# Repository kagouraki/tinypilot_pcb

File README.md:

# tinypilot_pcb
This is my pcb for tinypilot

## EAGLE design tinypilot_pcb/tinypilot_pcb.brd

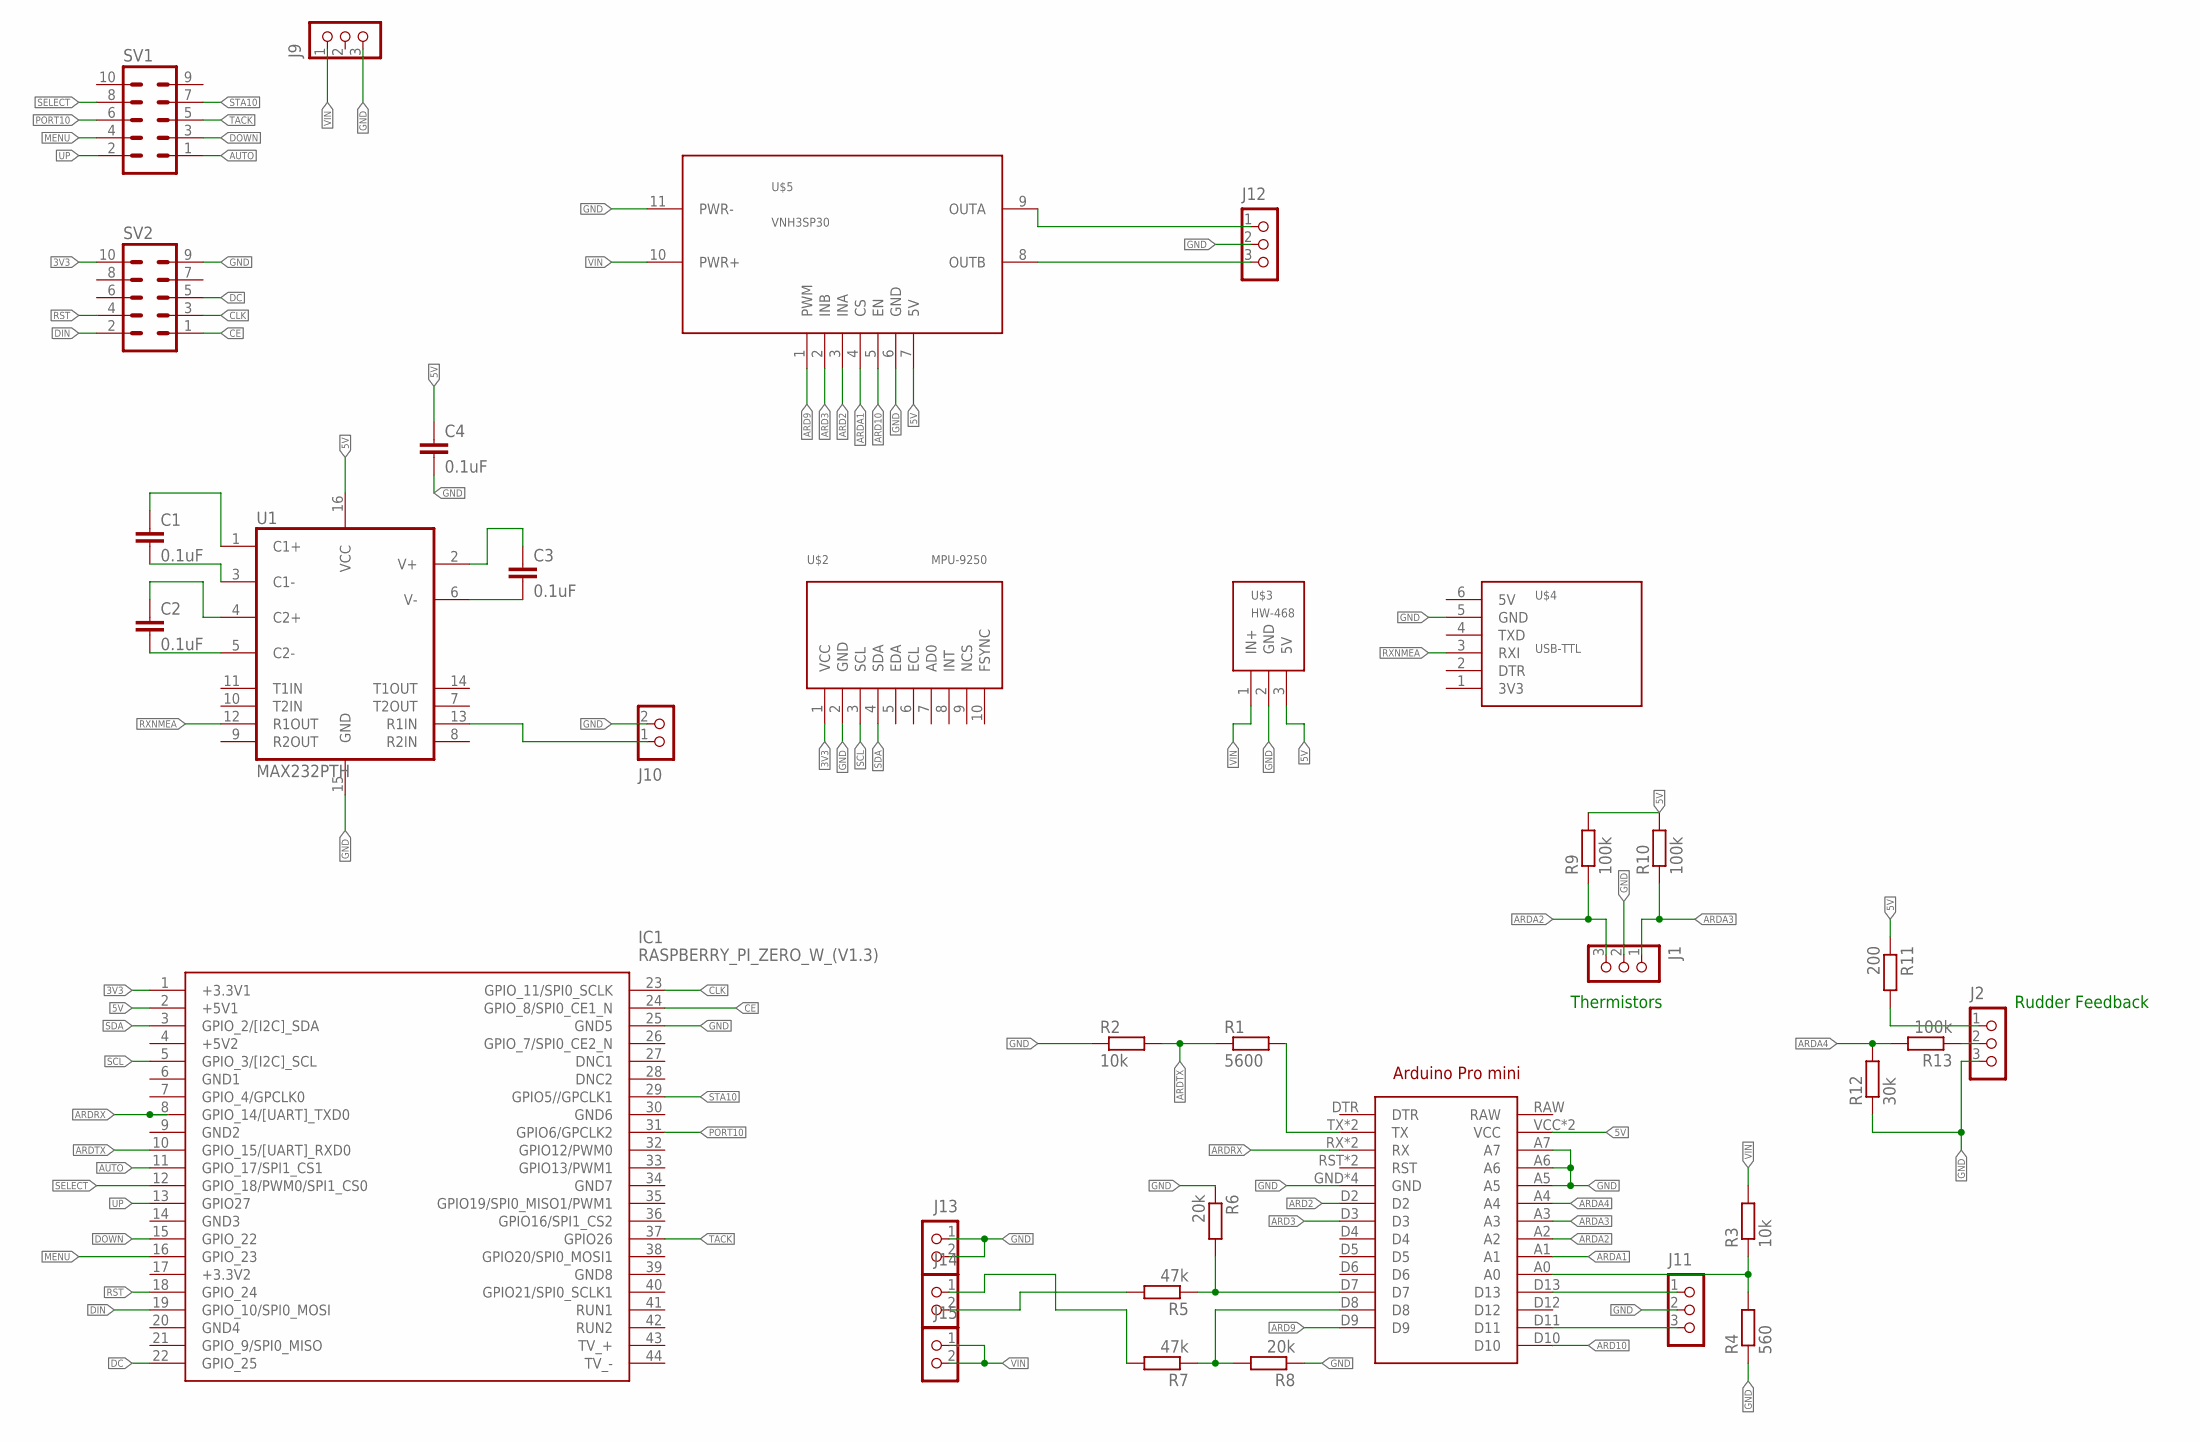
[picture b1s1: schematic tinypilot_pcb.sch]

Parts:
ARDUINO1: ARDUINO_PRO_MINI
C1, C2, C3, C4: 0.1uF; CAP-PTH-5MM
IC1: RASPBERRY_PI_ZERO_W_(V1.3); RASPBERRYPIZEROWV13
J1, J2, J9, J11, J12: CON_TERMINAL_BLOCK_03-5MM; TERMINAL_BLOCK_3P_5
J10, J13, J14, J15: CON_TERMINAL_BLOCK_02-5MM; TERMINAL_BLOCK_2P_5
R1: 5600; 0207/10
R2, R3: 10k; 0207/10
R4: 560; 0207/10
R5, R7: 47k; 0207/10
R6, R8: 20k; 0207/10
R9, R10, R13: 100k; 0207/10
R11: 200; 0207/10
R12: 30k; 0207/10
SV1, SV2: ML10
U1: MAX232PTH; DIL16
U$2: MPU-9250
U$3: HW-468
U$4: USB-TTL
U$5: VNH3SP30

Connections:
3V3: IC1.1 (+3.3V1), SV2.10, U$2.1 (VCC)
5V: ARDUINO1.VCC, ARDUINO1.VCC@1 (VCC), C4.1, IC1.2 (+5V1), R9.2, R10.2, R11.1, U1.16 (VCC), U$3.3 (5V), U$5.7 (5V)
ARD2: ARDUINO1.D2, U$5.3 (INA)
ARD3: ARDUINO1.D3, U$5.2 (INB)
ARD9: ARDUINO1.D9, U$5.1 (PWM)
ARD10: ARDUINO1.D10, U$5.5 (EN)
ARDA1: ARDUINO1.A1, U$5.4 (CS)
ARDA2: ARDUINO1.A2, J1.3, R9.1
ARDA3: ARDUINO1.A3, J1.1, R10.1
ARDA4: ARDUINO1.A4, R12.2, R13.2
ARDRX: ARDUINO1.RX, ARDUINO1.RX@1 (RX), IC1.8 (GPIO_14/[UART]_TXD0)
ARDTX: IC1.10 (GPIO_15/[UART]_RXD0), R1.1, R2.2
AUTO: IC1.11 (GPIO_17/SPI1_CS1), SV1.1
CE: IC1.24 (GPIO_8/SPI0_CE1_N), SV2.1
CLK: IC1.23 (GPIO_11/SPI0_SCLK), SV2.3
DC: IC1.22 (GPIO_25), SV2.5
DIN: IC1.19 (GPIO_10/SPI0_MOSI), SV2.2
DOWN: IC1.15 (GPIO_22), SV1.3
GND: ARDUINO1.A5, ARDUINO1.A6, ARDUINO1.A7, ARDUINO1.GND, ARDUINO1.GND@1 (GND), ARDUINO1.GND@2 (GND), ARDUINO1.GND@3 (GND), C4.2, IC1.25 (GND5), J1.2, J2.3, J9.3, J10.2, J11.2, J12.2, J13.1, J13.2, R2.1, R4.1, R6.1, R8.1, R12.1, SV2.9, U1.15 (GND), U$2.2 (GND), U$3.2 (GND), U$4.5 (GND), U$5.6 (GND), U$5.11 (PWR-)
MENU: IC1.16 (GPIO_23), SV1.4
unnamed: C1.1, U1.1 (C1+)
unnamed: C1.2, U1.3 (C1-)
unnamed: C2.1, U1.4 (C2+)
unnamed: C2.2, U1.5 (C2-)
unnamed: C3.2, U1.6 (V-)
unnamed: C3.1, U1.2 (V+)
unnamed: J14.2, R5.2
unnamed: J12.1, U$5.9 (OUTA)
unnamed: J12.3, U$5.8 (OUTB)
unnamed: ARDUINO1.D13, J11.1
unnamed: ARDUINO1.D11, J11.3
unnamed: ARDUINO1.A0, R3.1, R4.2
unnamed: ARDUINO1.D7, R5.1, R6.2
unnamed: ARDUINO1.TX, ARDUINO1.TX@1 (TX), R1.2
unnamed: ARDUINO1.D8, R7.1, R8.2
unnamed: J14.1, R7.2
unnamed: J2.1, R11.2
unnamed: J2.2, R13.1
PORT10: IC1.31 (GPIO6/GPCLK2), SV1.6
R1IN: J10.1, U1.13 (R1IN)
RST: IC1.18 (GPIO_24), SV2.4
RXNMEA: U1.12 (R1OUT), U$4.3 (RXI)
SCL: IC1.5 (GPIO_3/[I2C]_SCL), U$2.3 (SCL)
SDA: IC1.3 (GPIO_2/[I2C]_SDA), U$2.4 (SDA)
SELECT: IC1.12 (GPIO_18/PWM0/SPI1_CS0), SV1.8
STA10: IC1.29 (GPIO5//GPCLK1), SV1.7
TACK: IC1.37 (GPIO26), SV1.5
UP: IC1.13 (GPIO27), SV1.2
VIN: J9.1, J15.1, J15.2, R3.2, U$3.1 (IN+), U$5.10 (PWR+)

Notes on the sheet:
Thermistors
Rudder Feedback

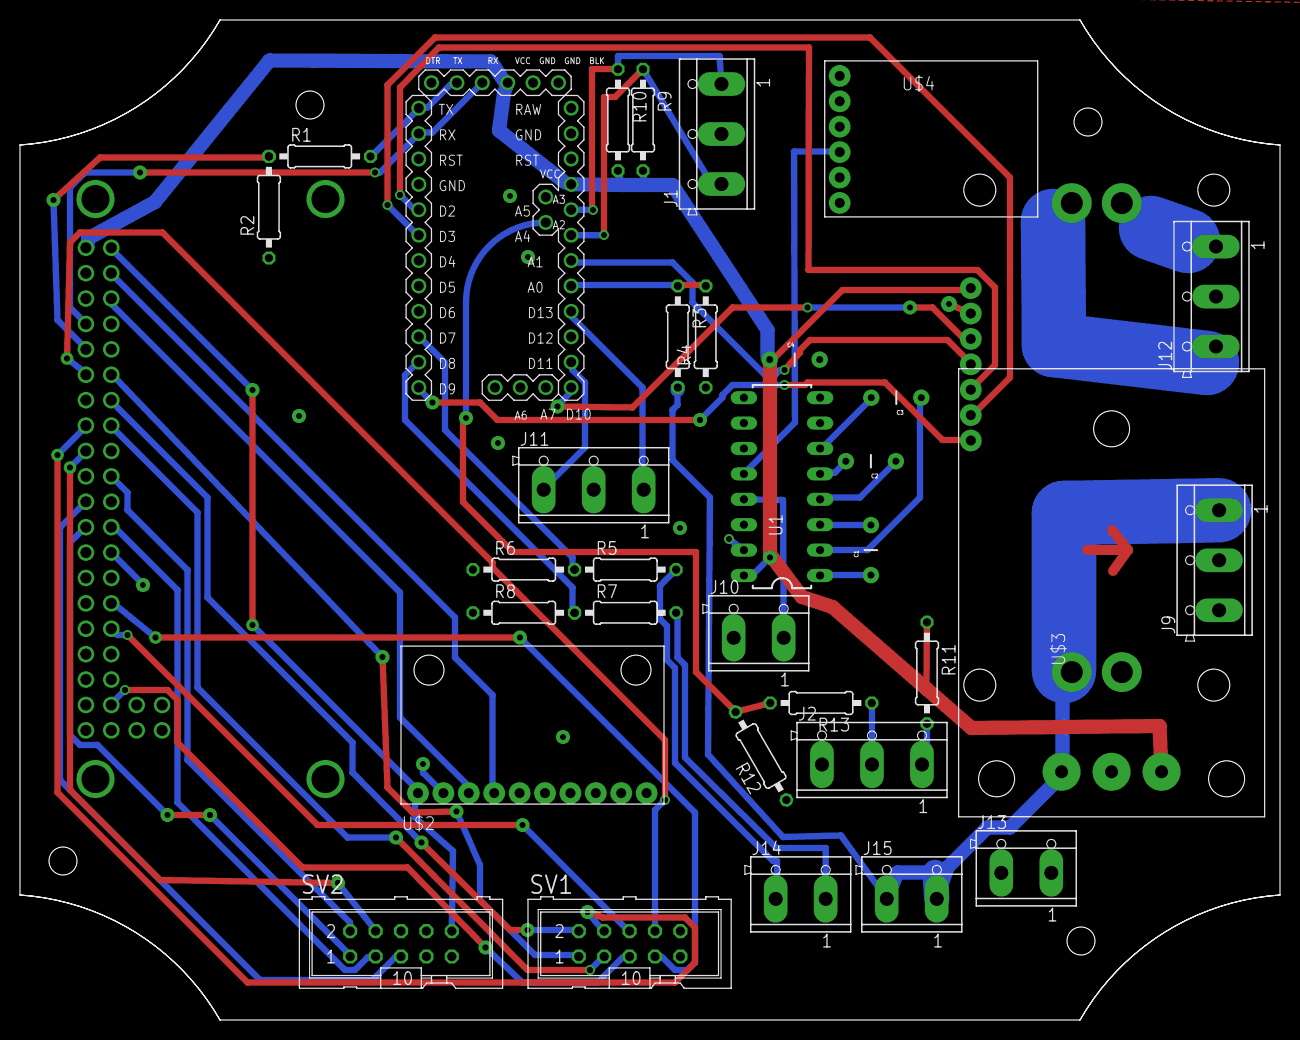
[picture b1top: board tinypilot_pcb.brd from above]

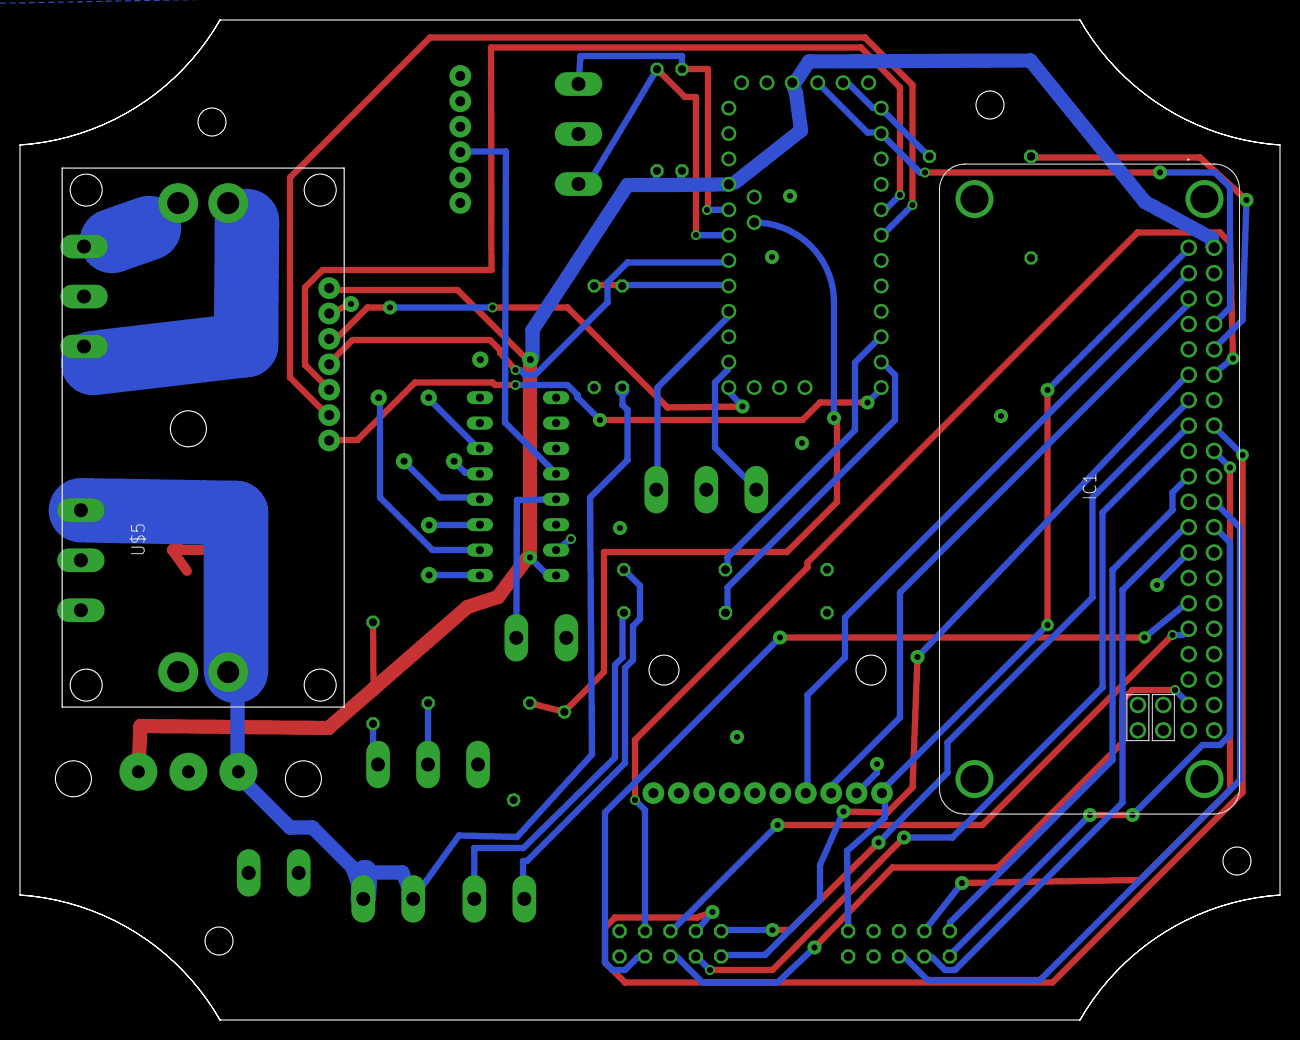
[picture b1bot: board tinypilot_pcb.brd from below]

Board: 2 copper layers, 126.0 x 100.0 mm, 35 parts (2 on the bottom side), 49 nets.

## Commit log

2022-05-22 Initial add files
